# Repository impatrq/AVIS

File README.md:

# AVIS - Simulador de Vuelo Inmersivo

<div align="center">
  
  <h3>Ayudando a la formacion de futuros técnicos y pilotos</h3>
  <p>Simulador de vuelo realista e inmersivo con estructura movil e instrumentos funcionales</p>
  
  <!-- Íconos de redes sociales -->
<p align="center">
  &nbsp;&nbsp;&nbsp;&nbsp;
  &nbsp;&nbsp;&nbsp;&nbsp;
  
</p>
</div>

## 🌐 Accede a la Página Web

🔗 [Visita la Web de AVIS](https://lautarocabeza.github.io/proyecto.avis/)

## ✨ Ayudando a la formacion de Técnicos y Pilotos

AVIS es un simulador de vuelo educativo diseñado para proporcionar una experiencia inmersiva y realista de pilotaje de aeronaves, recreando con precisión la cabina de un Cessna 172, una de las aeronaves de entrenamiento más populares del mundo.

## 🔧 Características Principales

- **Estructura Movil**: Avis integra tecnología de movimiento físico para simular las sensaciones reales que experimenta un piloto durante el vuelo.
- **Cabina Realista**: La cabina será idéntica a la de la aeronave Cessna 172, proporcionando al futuro técnico/piloto aprender de forma realista.
- **Instrumentación Realista**: Los instrumentos de la aeronave funcionarán con el vuelo, ayudando al futuro piloto a aprender o permitiendo a profesores enseñar a alumnos.
- **Sofware Avanzado**: Incluye un programa de simulación profesional con físicas de vuelo realista, condiciones meteorológicas variables y escenarios de emergencia.
- **Experiencia Inmersiva**: Integra pantallas de alta resolución y un sistema de sonido que reproduce con precisión los sonidos de la aeronave y del ambiente.
- **Versátil**: Emula una variedad de situaciones, con locaciones reales y pistas reales en diversos lugares del mundo sin correr riesgos.
- **Certificación**: Se buscará la certificación del simulador para que se puedan sumar horas de vuelo para aprendices de piloto.

## 👨‍👩‍👦🛠️ Aplicaciones

- **Profesores de la Escuela**: Avis permite enseñarle a los estudiantes sobre instrumentación, sistemas de navegación, y demás características de la aeronave.
- **Pilotos en Formación**: Ayuda de forma segura y controlada a las personas que buscan aprender a pilotar.
- **Horas de Vuelo**: Con el simulador certificado permitiria a los pilotos sumar horas de vuelo usando nuestro producto.

## ⚡ Tecnología Utilizada

- **Hardware**:

  - Raspberry pi pico 2
  - Sensores de posición
  - Motores trifásicos con caja reductora
  - Estructura con movimiento en 2 ejes
  - Cabina con switches, pantallas y encoders
  - Volante de avión realista
  - Computadora para la simulacion

- **Software**:
  - Programación en C/C++ y Python
  - Integración de sistemas de la cabina en la simulación
  - Funcionamiento de periféricos como el volante en la simulación
  - Sincronización entre la simulación del avión y la cabina física

## 💸 Costos Estimados

El desarrollo de AVIS tiene un costo aproximado de **6000 USD**, incluyendo la estructura de metal, componentes electrónicos, motores, displays y tecnologías integradas.

## 📢 Contribución

Si deseas colaborar con el desarrollo de AVIS, puedes comunicarte al Mail:
simulador.avis@gmail.com

## Integrantes:

### Lautaro Cabeza

- 📷 Instagram: [@lautiicabezaa](https://www.instagram.com/lautiicabezaa)
- 📧 Mail: lautiicabezaaa@gmail.com
- 🌐 Github: [LautaroCabeza](github.com//LautaroCabeza)

### Bruno Colombo

- 📷 Instagram: [@brunoo.colombo](https://www.instagram.com/brunoo.colombo)
- 📧 Mail: bruno.colombo.genlot@gmail.com
- 🌐 Github: [brunoocolombo](https://github.com/brunoocolombo)

### Mateo Coria Reartes

- 📷 Instagram: [@coriaa.f1](https://www.instagram.com/coriaa.f1)
- 📧 Mail: mateocoria879@gmail.com
- 🌐 Github: [mateocoria02](https://github.com/mateocoria02)

### Natanael Robaina

- 📷 Instagram: [@natarobaina](https://www.instagram.com/natarobaina)
- 📧 Mail: natarob2006@outlook.com
- 🌐 Github: [Robaina1](https://github.com/Robaina1)

### Juan Pablo Rodriguez

- 📷 Instagram: [@juanka.rod](https://www.instagram.com/juanka.rod)
- 📧 Mail: juamppa@icloud.com
- 🌐 Github: [JuanPablo2905](https://github.com/JuanPablo2905)

### Vicente Seta

- 📷 Instagram: [@vicen_007](https://www.instagram.com/vicen_007)
- 📧 Mail: vicenseta@gmail.com
- 🌐 Github: [setavicente](https://github.com/setavicente)

### Luca Sturla

- 📷 Instagram: [@](https://www.instagram.com/)
- 📧 Mail: 
- 🌐 Github: 

### Tomas Vogel

- 📷 Instagram: [@goyovogel](https://www.instagram.com/goyovogel)
- 📧 Mail: gregoriovogel@gmail.com
- 🌐 Github: [TomasGoyo](https://github.com/TomasGoyo)

---

Avis busca mejorar los metodos de aprendizaje en la escuela. ¡Sé parte de la revolución! 💪🛠

## 📜 Licencia

Este proyecto está licenciado bajo la [MIT License](LICENSE).  
© 2025 Avis.corp.

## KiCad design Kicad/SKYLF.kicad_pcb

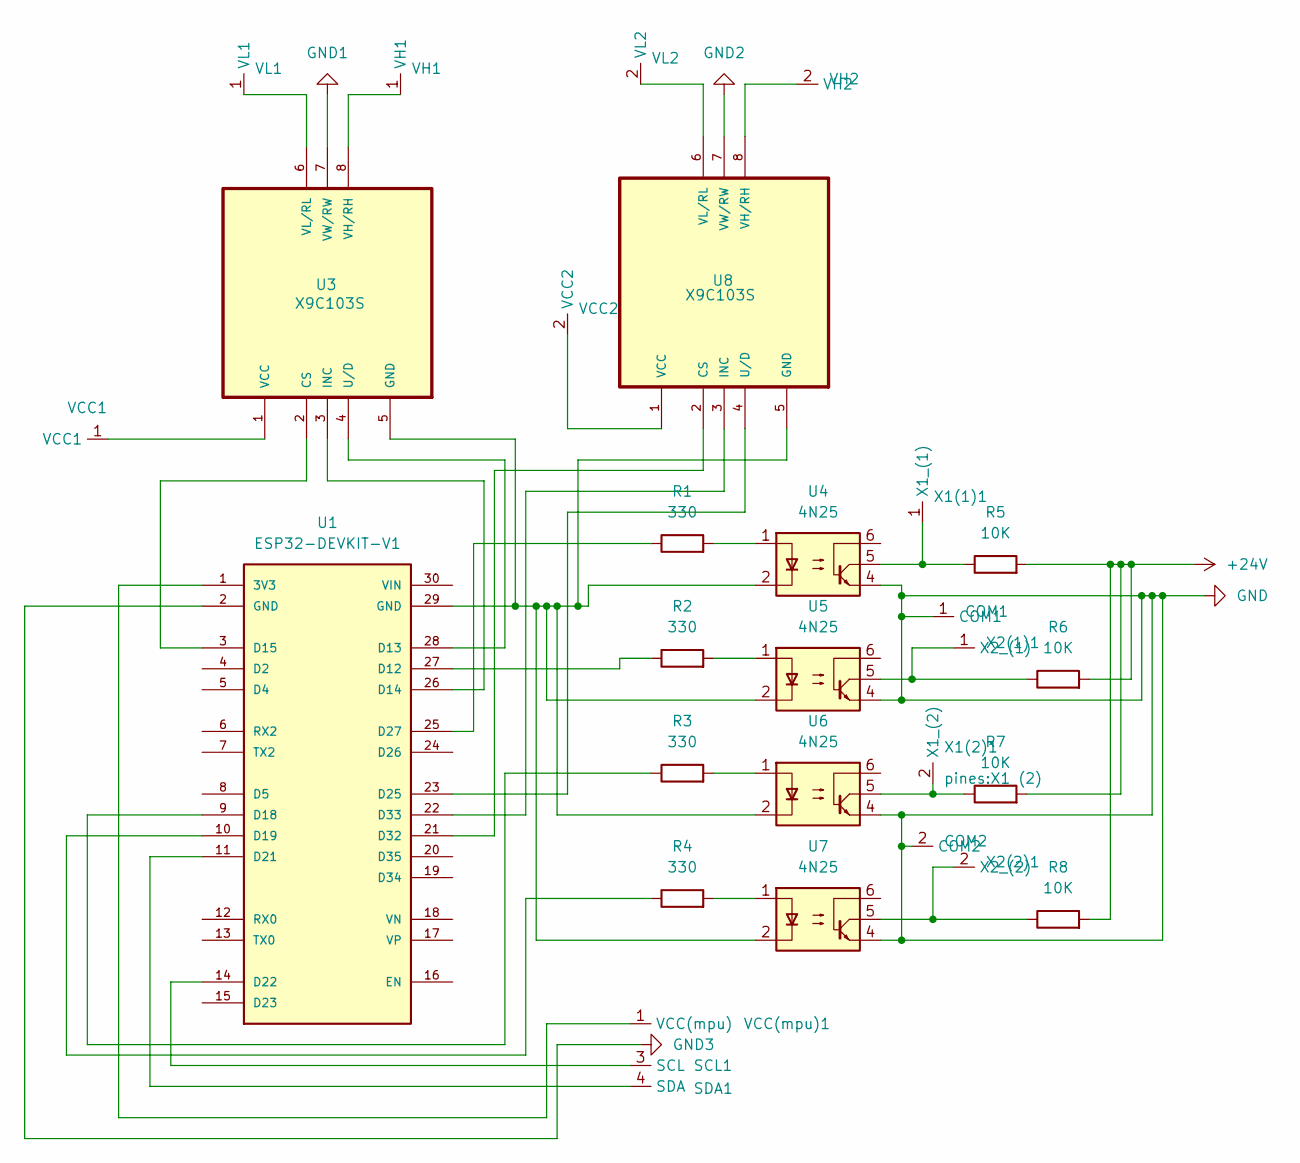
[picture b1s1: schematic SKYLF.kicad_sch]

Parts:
COM1: COM1
COM2: COM2
R1, R2, R3, R4: 330; R_Axial_DIN0309_L9.0mm_D3.2mm_P12.70mm_Horizontal
R5, R6, R7, R8: 10K; R_Axial_DIN0309_L9.0mm_D3.2mm_P12.70mm_Horizontal
SCL1: SCL
SDA1: SDA
U1: ESP32-DEVKIT-V1; MODULE_ESP32_DEVKIT_V1; PARTREV N/A
U3, U8: X9C103S; Potenciometro X9C103S; MPN X9C103S
U4, U5, U6, U7: 4N25; DIP-6_W7.62mm
VCC1: VCC1
VCC2: VCC2
VCC(mpu)1: VCC (mpu)
VH1: VH1
VH2: VH2
VL1: VL1
VL2: VL2
X1(1)1: X1 (1)
X1(2)1: X1 (2)
X2(1)1: X2 (1)
X2(2)1: X2 (2)

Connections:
+24V: R5.2, R6.2, R7.2, R8.2
GND: COM1.1 (COM1), COM2.2 (COM2), U4.4, U5.4, U6.4, U7.4
GND1: U3.7 (VW/RW)
GND2: U8.7 (VW/RW)
GND3: U1.2 (GND)
unnamed: R1.2, U4.1
unnamed: R2.2, U5.1
unnamed: R3.2, U6.1
unnamed: R4.2, U7.1
unnamed: SCL1.3 (SCL), U1.14 (D22)
unnamed: SDA1.4 (SDA), U1.11 (D21)
unnamed: U1.1 (3V3), VCC(mpu)1.1 (VCC(mpu))
unnamed: R2.1, U1.27 (D12)
unnamed: U1.28 (D13), U3.4 (U/D)
unnamed: U1.26 (D14), U3.3 (INC)
unnamed: U1.3 (D15), U3.2 (CS)
unnamed: R3.1, U1.9 (D18)
unnamed: R4.1, U1.10 (D19)
unnamed: U1.23 (D25), U8.4 (U/D)
unnamed: R1.1, U1.25 (D27)
unnamed: U1.21 (D32), U8.2 (CS)
unnamed: U1.22 (D33), U8.3 (INC)
unnamed: U1.29 (GND), U3.5 (GND), U4.2, U5.2, U6.2, U7.2, U8.5 (GND)
unnamed: U3.1 (VCC), VCC1.1 (VCC1)
unnamed: U3.8 (VH/RH), VH1.1 (VH1)
unnamed: U3.6 (VL/RL), VL1.1 (VL1)
unnamed: U8.1 (VCC), VCC2.2 (VCC2)
unnamed: U8.8 (VH/RH), VH2.2 (VH2)
unnamed: U8.6 (VL/RL), VL2.2 (VL2)
unnamed: R5.1, U4.5, X1(1)1.1 (X1_(1))
unnamed: R7.1, U6.5, X1(2)1.2 (X1_(2))
unnamed: R6.1, U5.5, X2(1)1.1 (X2_(1))
unnamed: R8.1, U7.5, X2(2)1.2 (X2_(2))

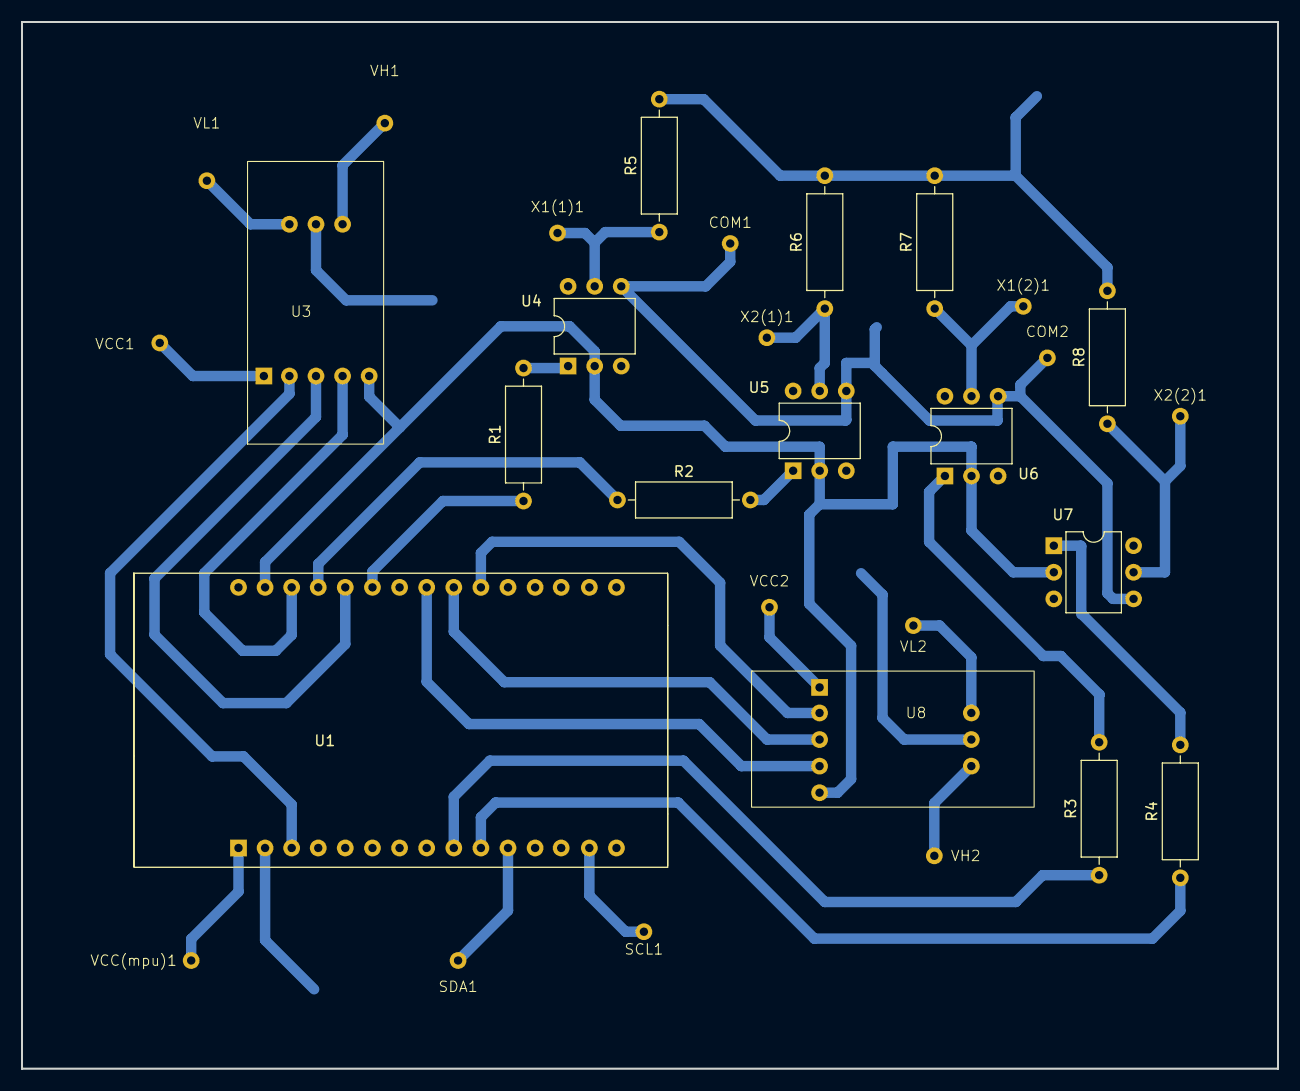
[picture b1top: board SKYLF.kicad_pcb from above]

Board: 2 copper layers, 120.0 x 100.0 mm, 30 parts (0 on the bottom side), 30 nets.

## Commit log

2024-04-30 variables
    Una lista de todas las variables que se pueden llegar a utilizar para, por ejemplo, mover la cabina o para tener las indicaciones de los instrumentos
2024-05-14 Create Documentos
    Acá están los documentos de las variables de simulación, de como extraerlos y de como conectar el ESP32 con el RS485 y el MPU6050
2024-11-11 Factura de compra cables macho-macho
2024-11-11 Factura de compra 10 tornillos y arandelas
2024-11-13 llave selectora
2024-11-15 cambio de nombre
2024-11-15 Codigo de pueba N° entre el ESP32 y el Pote digital
2024-11-15 Codigo de pueba N°1 entre el ESP32 y el Pote digital
2024-11-15 Create Codigo de pueba N°2 entre el ESP32 y el Pote digital
2024-11-15 Create Codigo de pueba N°1 entre el ESP32 y el Pote digital con el MPU6050
2024-11-15 Create Codigo de pueba N°2 entre el ESP32 y el Pote digital con el MPU6050
2024-11-15 Create Codigo de pueba N°3 entre el ESP32 y el Pote digital con el MPU6050
2024-11-15 Create Codigo de pueba N°4 entre el ESP32 y el Pote digital con el MPU6050
2024-11-15 Create Codigo de pueba N°5 entre el ESP32 y el Pote digital con el MPU6050 (con un filtro)
2024-11-20 Create MPU6050_light
2024-11-21 imagenes de la pagina web
2024-11-26 Informe descriptivo actualizado
2024-11-27 Github de todos los integrantes
2024-11-27 gmail de contacto de cada integrante en la caratula del github
2024-11-27 Contactos de cada integrante en la caratula del Github
2024-11-27 Organización de la distribución de la caratula del GitHub
2024-11-27 Foto grupal de SKYLF
2024-11-27 Video de Presentación SKYLF
2024-11-27 Organizar laa carpetas de panel de control en el github
2024-11-28 Factura de compra scaneada de MPU6050 del 14-10
2024-11-28 agregar WASM
2024-11-28 archivos mofiflight
2024-12-11 Diciembre
2024-12-11 fix: se corrige nombre a archivos
2024-12-11 Informe descr. Diagrama
2024-12-11 Actualizar C.c Noviembre.txt
2024-12-11 Actualizar (20/11) C.c Noviembre.txt
2024-12-11 campo
2024-12-11 mayo
2024-12-11 julio
2024-12-11 agosto
2024-12-11 Plantilla de gastos del proyecto
2024-12-16 Inf descriptivo en PDF
2024-12-17 Carpeta técnica actualizacion
2024-12-17 feat: agregar carpeta de campo
2024-12-17 kicad
2024-12-17 pag web
2024-12-17 deed
2024-12-17 redes chau
2024-12-18 Create Link a youtube
2024-12-19 Gasto total de SKYLF
2025-04-30 feat: Creo la logica del Yoke
2025-05-07 Feat: Creo el archivo para las pruebas con el sensor
2025-05-07 feat: Diseño de la placa del yoke
2025-05-08 Feat: Creo la lectura de datos del fstelemetry
2025-05-08 feat: adaptacion del codigo para la pico zero
2025-05-08 Feat: Agrego la lectura de fstelemetry por la RP2040
2025-05-08 Fix: Cambio en el CMakeLists.txt
2025-05-08 Feat:Conversion de unidades desde la PIco
2025-05-08 Fix: Saco un simbolo para poder hacer la lectura desde la RP2040
2025-05-09 feat:agrego manuales del variador
2025-05-09 feat: Creacion del documento de avances
2025-05-09 feat: Creacion de carpeta de media y foto del proceso
2025-05-09 feat: Añadimos contenido en el documento de avances
2025-05-09 feat: Agrego fotos y videos a la carpeta de media
2025-05-13 feat: Subimos fotos del proceso
2025-05-27 feat: agrego media del proyecto
2025-05-27 feat: Update README.md
2025-05-28 Feat: Añado word para llevar registro de los parametros modificados en gtake
2025-05-28 feat: actualizacion del registro de parametros modificados
2025-05-28 feat: agregamos contenido a avances
2025-06-05 Añado la modulacion PWM para la entrada de los variadores
2025-06-06 feat Manual variador danfoss
2025-06-10 feat: arranco a probar la comunicacion
2025-06-13 feat: Agrego manual de variador danfoss
2025-06-13 Feat: Añado codigo de MPU6050
2025-06-17 feat: comienzo del codigo de comunicacion
2025-06-17 feat: errores corregidos
2025-06-17 feat añado cambios realizados hasta la fecha
2025-06-19 feat: codigo por comunicacion wifi
2025-06-19 feat: update app.c
2025-06-19 feat: update mpu w
2025-06-26 feat: añado codigo funcionando para setear un angulo
2025-08-08 Añado el codigo de teclado angle pero con freertos
2025-08-10 Agrego la lectura de datos del juego
2025-10-29 BREAKING CHANGE: Modifico a la logica final del proyecto
    -Borro la tarea de LCD
    -Agrego filtro de kalman
    -Agrego control para variadores
    -Agrego extraccion de ambos ejes del flight simulator
    -Agrego estructuras de datos del sensor y del simulador de vuelo.
    -Saco el PWM
2025-10-29 Feat: Agrego cambios en el lector del CSV
    -El script run_fstelemetry,py hace que la velocidad del la extraccion de datos sea mas rapida
    -El Lector ahora retorna tanto pitch como rol. Ademas que espera a la sincronizacion con el script fstelemetry antes de cargar los datos
    - A el cofing.yaml se le agrego el angulo de roll
2025-11-07 Create Documentación
2025-11-11 feat: Agrego lectura de los ultimos datos disponibles, con actualizacion de 0,5
    Ademas agrego el generator.py, en caso de tener que probar la comunicacion con la pico sin necesidad de el flight simulator.
2025-11-13 Feat: Cambio en la logica de funcionamiento del yoke
    - Convierto a lineal las medidas del potenciometro
2025-11-17 feat: añado esquemático de la placa YOKE
2025-11-17 feat: añado esquematico de la placa YOKE
2025-11-17 Create GARMIN_G-1000
2025-11-17 feat: añado esquemáticos del GARMIN G-1000
2025-11-17 feat: añado esquemáticos de las placas del panel
2025-11-17 feat: Add PCB section
2025-11-18 Create impresiones 3d
2025-11-18 feat: añado esquemáticos
2025-11-18 feat: añado carpeta para las pcb´s
2025-11-18 feat : elimiino archivos extra
2025-11-19 feat: añado pcbs de las placas para garmin g-1000
2025-11-24 feat:añado pcbs personales de placas del Panel
2025-11-24 feat: añado pcbs personales de placas del Panel
2025-11-24 feat: añado esquemáticos personales de placas del Garmin
2025-11-24 feat: añado esquemáticos personales de placas del Panel
2025-12-03 Feat: Añado planos del panel de la cabina
2025-12-03 minor: agrego comentarios explicativos
2025-12-04 BREAKING CHANGE: Agrego el variadores DANFOSS
    -Correccion en las queues
    -Limitacion de angulo
2025-12-04 Create parametros danfoss
    lista de parametros del variador danfoss
2025-12-04 Create parametros_danfoss.md
    Agrego lista de parametros del variador danfoss
2025-12-04 Create Parametros-Gtake.md
    Agrego parametros del variador Gtake (aunque le faltan algunos los cuales hay que revisar en el variador)
2026-01-03 agrego instrucciones y manual de usuario
